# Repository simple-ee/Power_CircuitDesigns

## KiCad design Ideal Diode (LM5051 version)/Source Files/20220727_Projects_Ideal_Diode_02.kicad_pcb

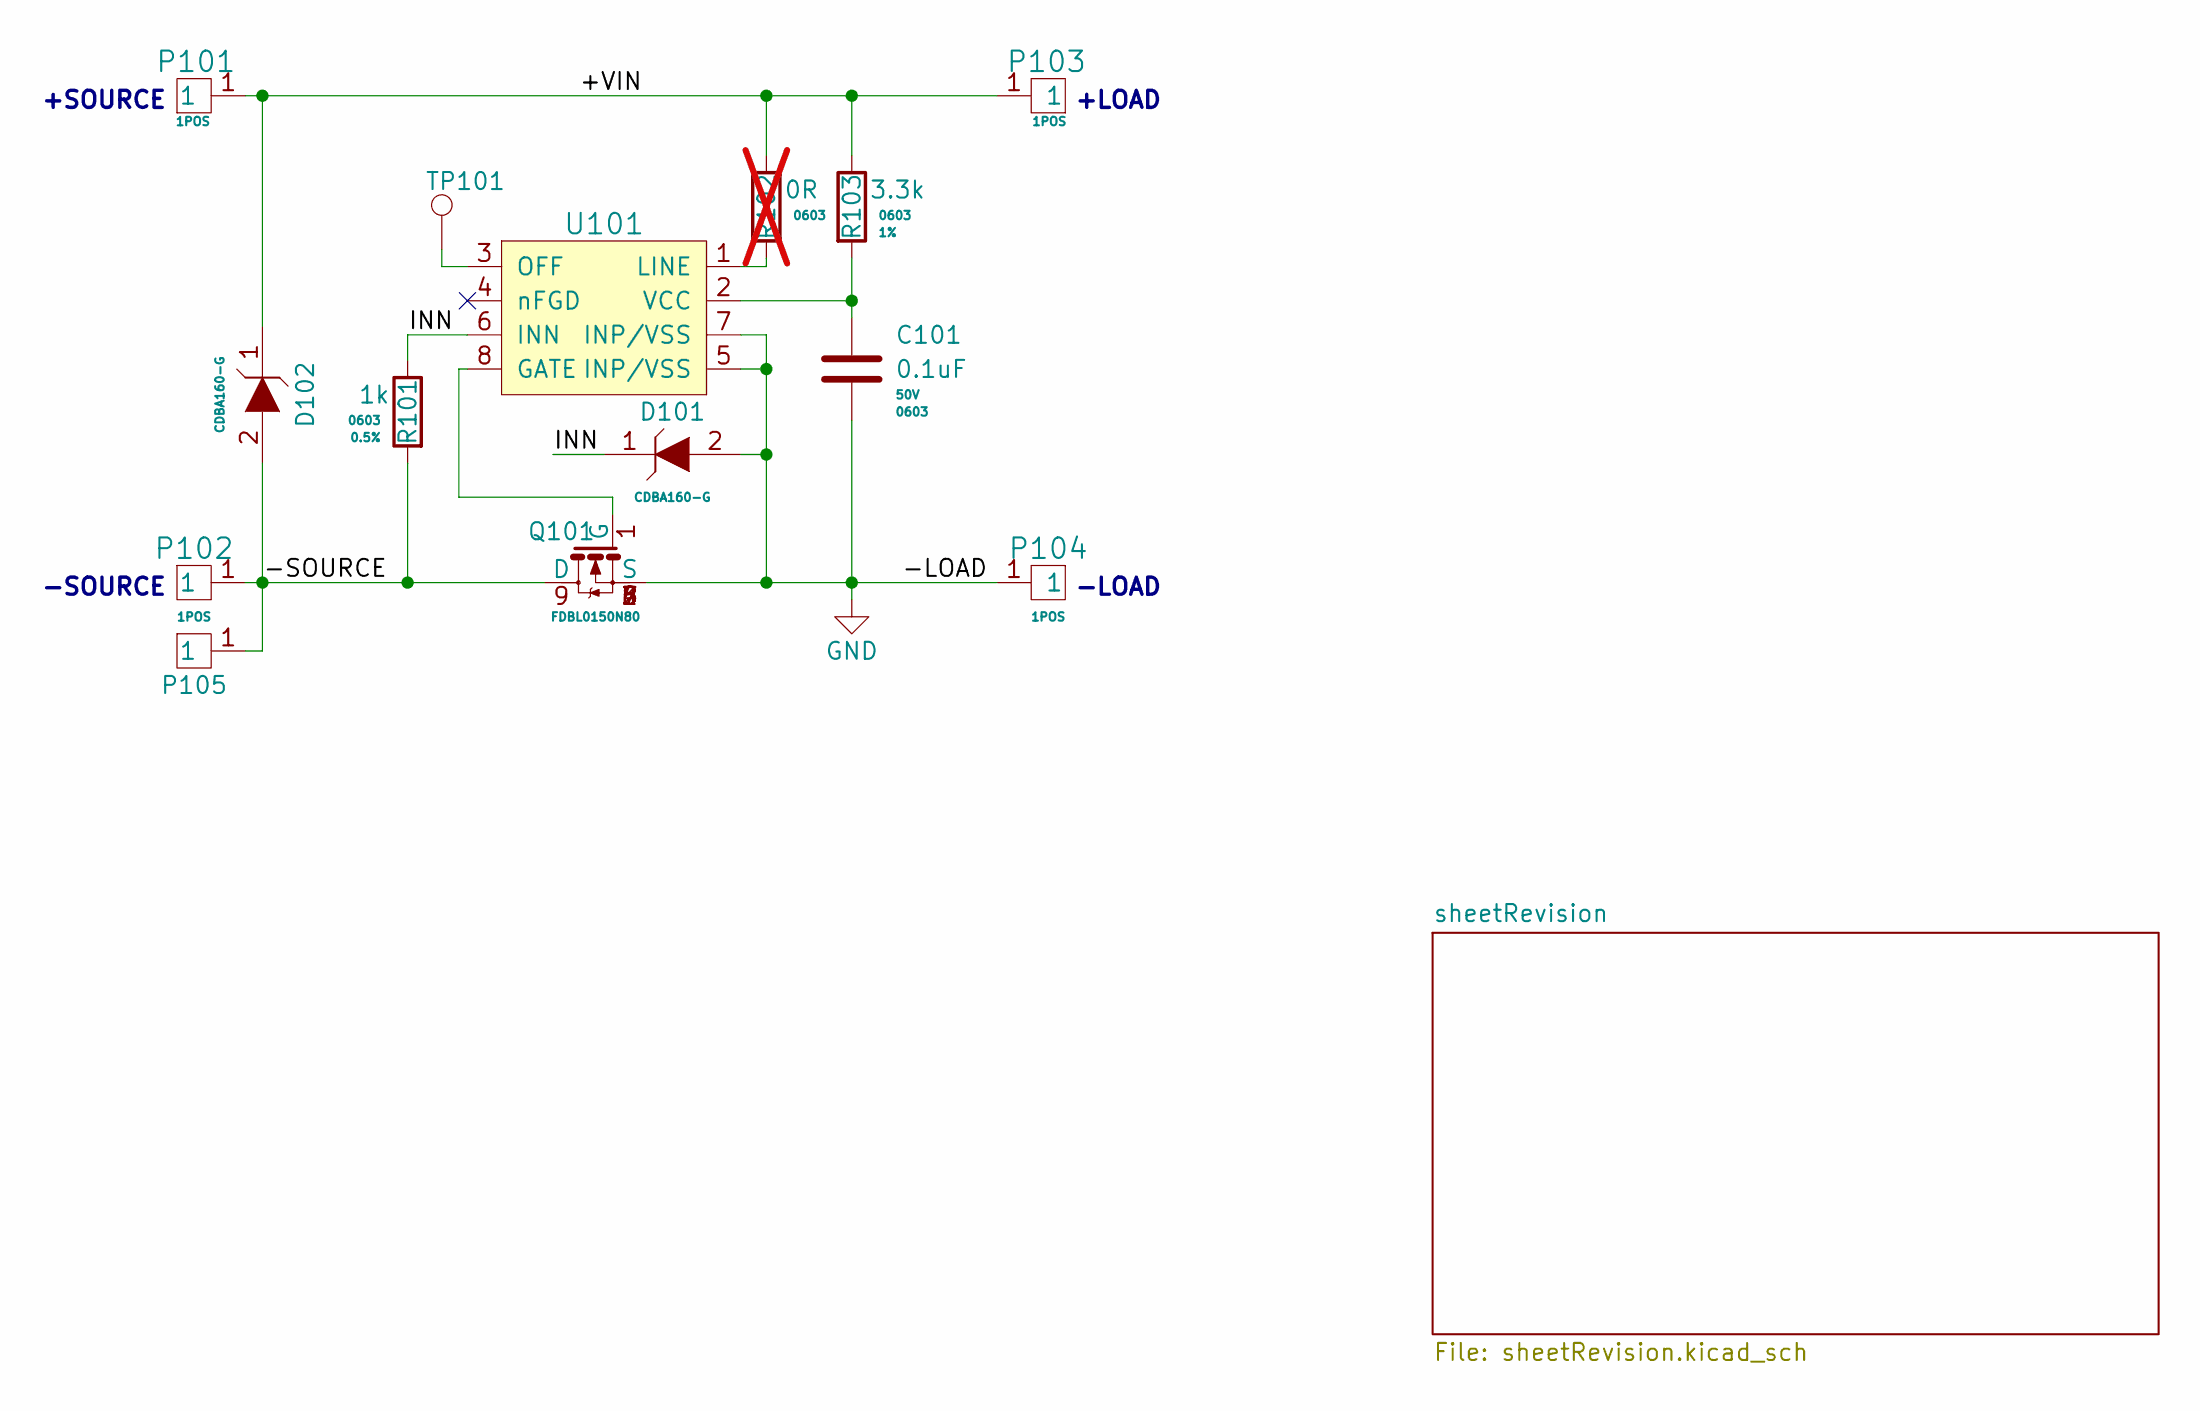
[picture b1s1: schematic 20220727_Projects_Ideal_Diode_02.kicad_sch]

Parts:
C101: C0603C104K5RACAUTO; C_0603_Handsolder
D101, D102: CDBA160-G; D_SMA
P101, P103: TH_1POS_3.4MM_M3; TH_1POS_3.4MMxM3
P102, P104: TH_1POS_12MM_M5; TH_1POS_12MMxM5
P105: Heatsink_28x28x10mm; Manufacturer ###
Q101: FDBL0150N80; HPSOF-8
R101: RR0816P-102-D; R_0603_Handsolder
R102: RMCF0603ZT0R00; R_0603_Handsolder; not fitted
R103: RC0603FR-073K3L; R_0603_Handsolder
TP101: TestPoint_D1MM; TestPoint_Pad_D1.0mm
U101: LM5051MAX_NOPB; SOIC-8

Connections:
/+VIN: D102.1 (K), P101.1, P103.1, R102.1, R103.1
/-SOURCE: D102.2 (A), P102.1, P105.1, Q101.9 (D), R101.2
/INN: D101.1 (K), R101.1, U101.6 (INN)
GND: C101.2, D101.2 (A), P104.1, Q101.2 (S), Q101.3 (S), Q101.4 (S), Q101.5 (S), Q101.6 (S), Q101.7 (S), Q101.8 (S), U101.5 (INP/VSS), U101.7 (INP/VSS)
unnamed: Q101.1 (G), U101.8 (GATE)
unnamed: R102.2, U101.1 (LINE)
unnamed: TP101.1, U101.3 (OFF)
unnamed: C101.1, R103.2, U101.2 (VCC)

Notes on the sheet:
-LOAD
+LOAD
-SOURCE
+SOURCE

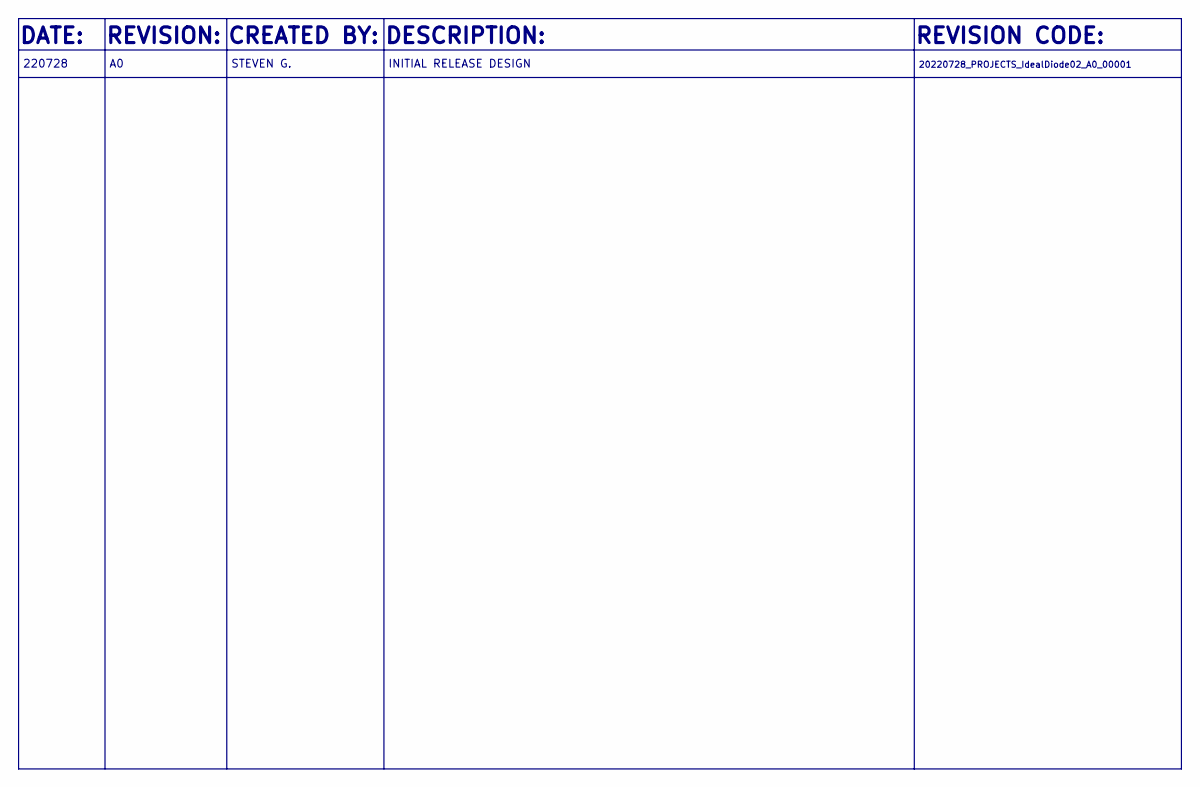
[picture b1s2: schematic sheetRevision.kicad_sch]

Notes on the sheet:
INITIAL RELEASE DESIGN
20220728_PROJECTS_IdealDiode02_A0_00001
220728
REVISION:
STEVEN G.
REVISION CODE:
DESCRIPTION:
DATE:
CREATED BY:

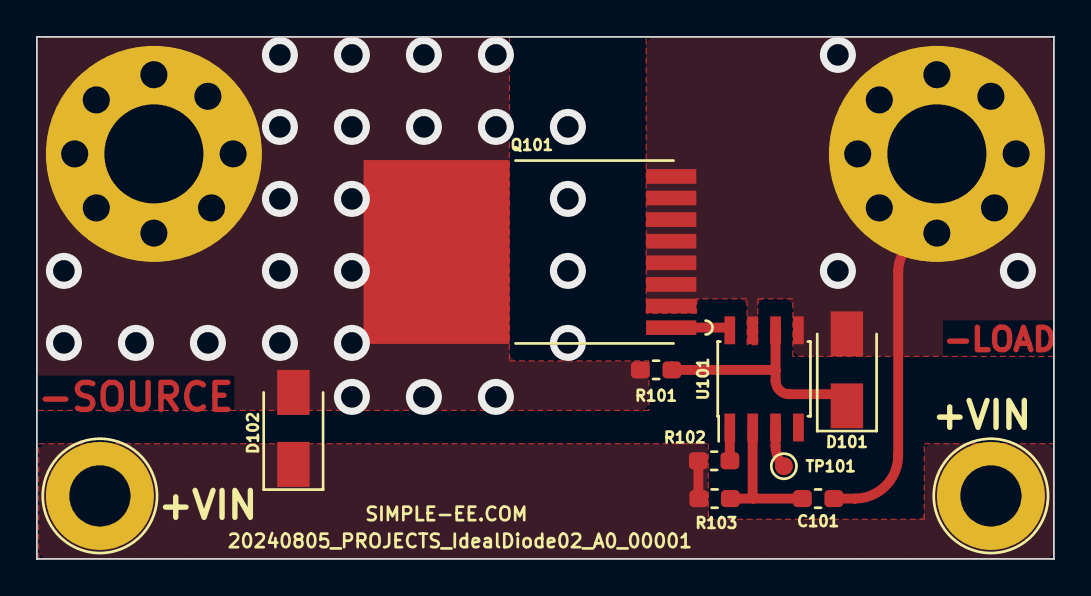
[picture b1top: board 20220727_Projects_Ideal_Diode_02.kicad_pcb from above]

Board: 2 copper layers, 56.5 x 29.0 mm, 14 parts (1 on the bottom side), 8 nets.

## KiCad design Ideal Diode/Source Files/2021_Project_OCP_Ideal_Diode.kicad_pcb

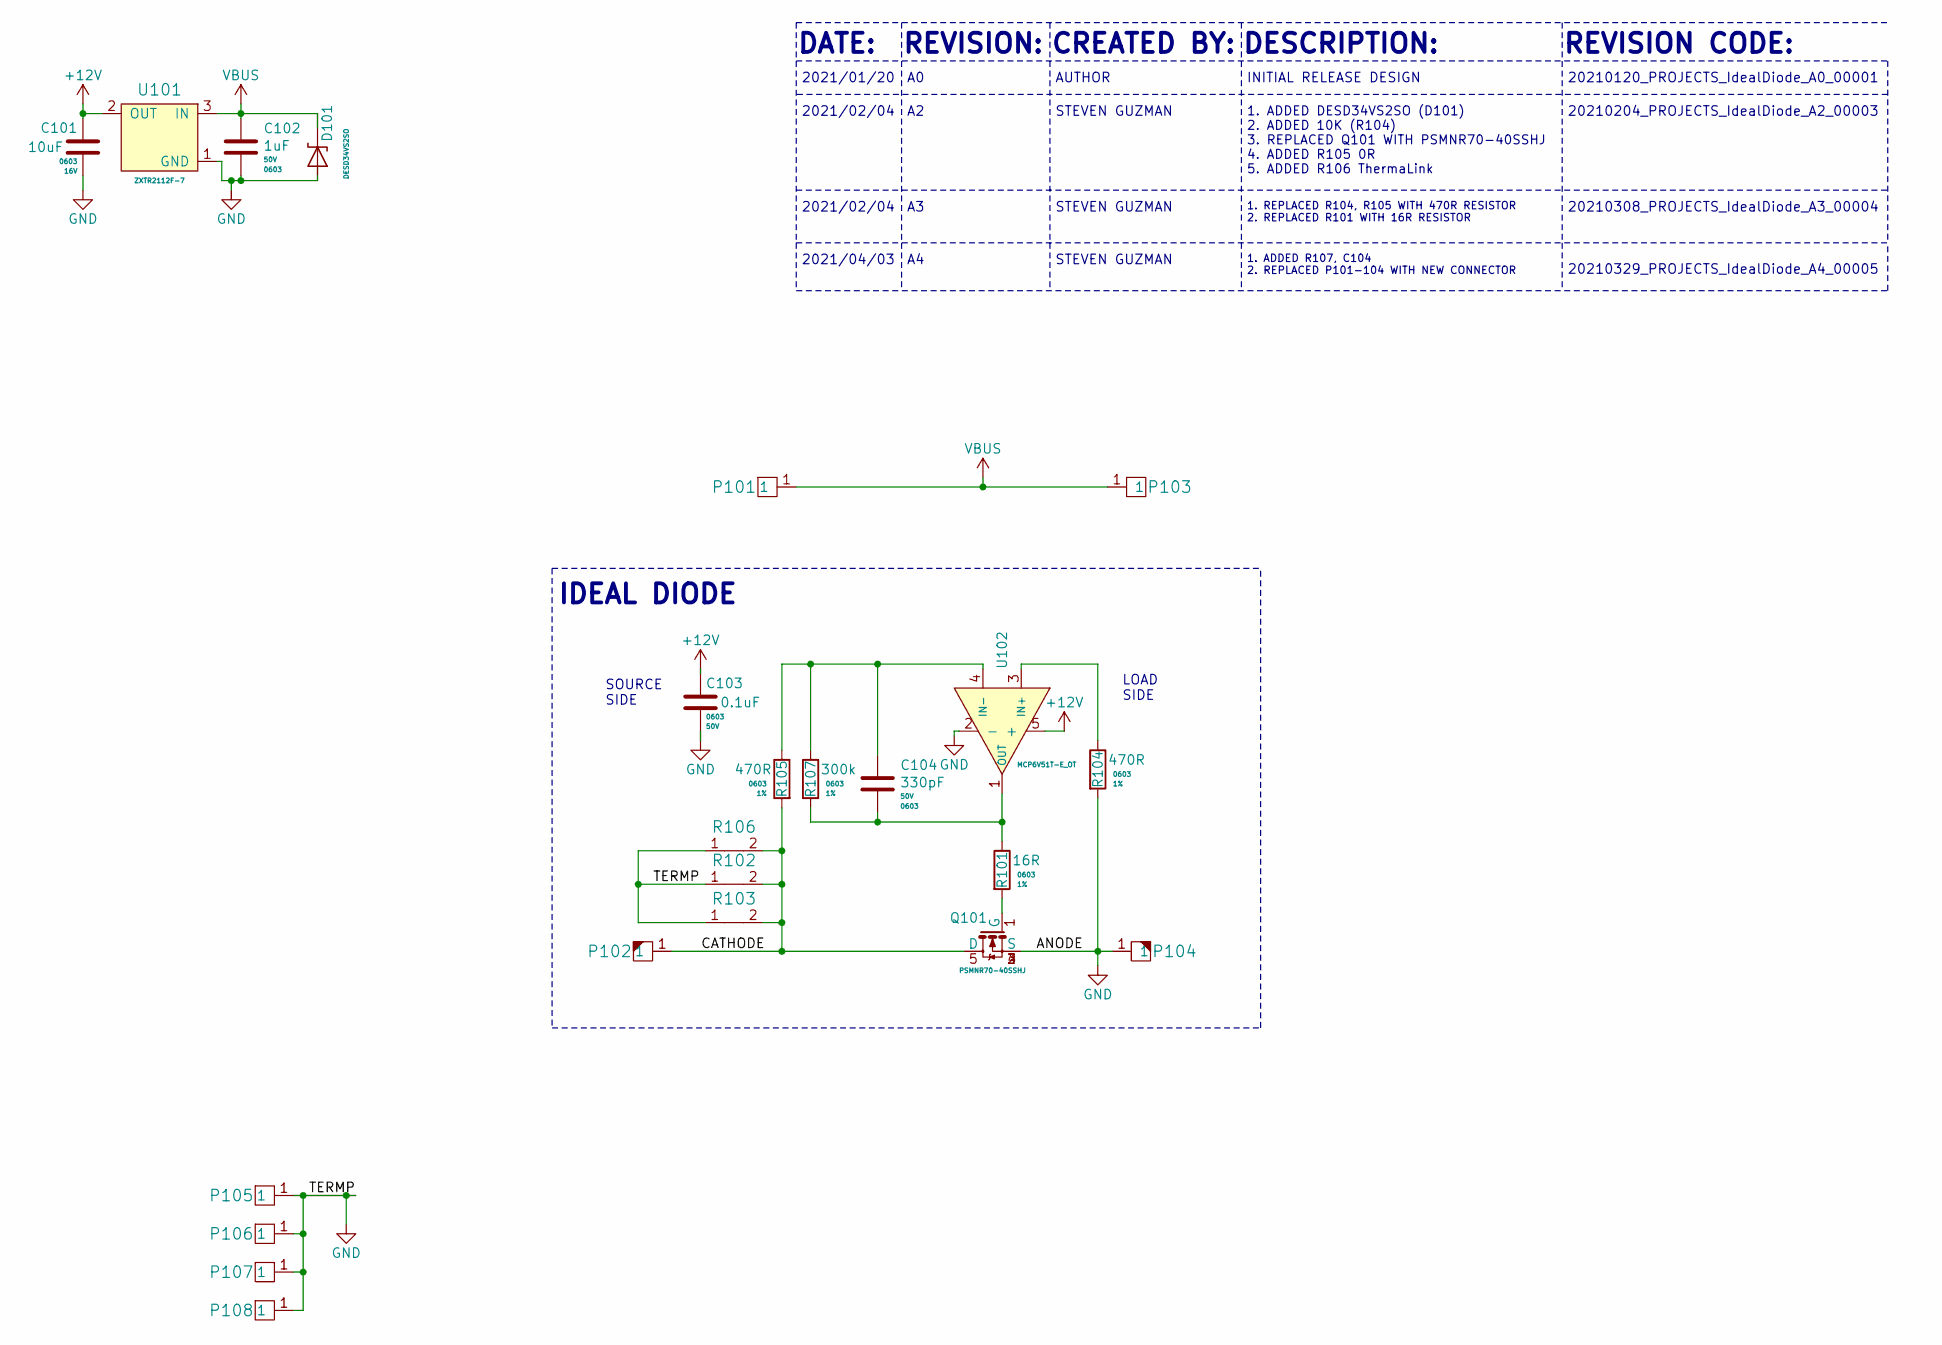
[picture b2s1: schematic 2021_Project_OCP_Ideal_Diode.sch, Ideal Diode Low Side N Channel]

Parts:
C101: CL10X106MO8NRNC; C_0603_Handsolder
C102: CL10A105KB8NNNC; C_0603_Handsolder
C103: C0603C104K5RACAUTO; C_0603_Handsolder
C104: C0603C331J5GACTU; C_0603_Handsolder
D101: DESD34VS2SO; SOT-23-3
P101, P103: 2.5x2.5mm_pad; pad_2.5x2.5mm
P102, P104: 7460305; 7460305_HASL
P105, P106, P107, P108: MH_1POS_2.5MM; MountingHole_2.5mm_Pad_Via
Q101: PSMNR70-40SSHJ; SOT-1235
R101: RC0603FR-0716RL; R_0603_Handsolder
R102, R103, R106: THJP0612AST1
R104, R105: RC0603FR-07470RL; R_0603_Handsolder
R107: RMCF0603FT300K; R_0603_Handsolder
U101: ZXTR2112F-7; SOT-23-3
U102: MCP6V51T-E_OT; SOT-23-5_HandSoldering

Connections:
+12V: C101.1, C103.1, U101.2 (OUT), U102.5 (+)
/CATHODE: P102.1, Q101.5 (D), R102.2, R103.2, R105.2, R106.2
GND: C101.2, C102.2, C103.2, D101.1 (A), D101.2 (A), P104.1, P105.1, P106.1, P107.1, P108.1, Q101.2 (S), Q101.3 (S), Q101.4 (S), R102.1, R103.1, R104.2, R106.1, U101.1 (GND), U102.2 (-)
unnamed: C104.1, R105.1, R107.1, U102.4 (IN-)
unnamed: C104.2, R101.1, R107.2, U102.1 (OUT)
unnamed: Q101.1 (G), R101.2
unnamed: R104.1, U102.3 (IN+)
VBUS: C102.1, D101.3 (K), P101.1, P103.1, U101.3 (IN)

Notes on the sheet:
DATE:
DESCRIPTION:
REVISION:
REVISION CODE:
2021/01/20
CREATED BY:
AUTHOR
20210120_PROJECTS_IdealDiode_A0_00001
SOURCE SIDE
LOAD SIDE
INITIAL RELEASE DESIGN
IDEAL DIODE
1. ADDED DESD34VS2SO (D101) 2. ADDED 10K (R104) 3. REPLACED Q101 WITH PSMNR70-40SSHJ 4. ADDED R105 0R 5. ADDED R106 ThermaLink
2021/02/04
20210204_PROJECTS_IdealDiode_A2_00003
STEVEN GUZMAN
1. REPLACED R104, R105 WITH 470R RESISTOR 2. REPLACED R101 WITH 16R RESISTOR
20210308_PROJECTS_IdealDiode_A3_00004
2021/04/03
1. ADDED R107, C104 2. REPLACED P101-104 WITH NEW CONNECTOR
20210329_PROJECTS_IdealDiode_A4_00005

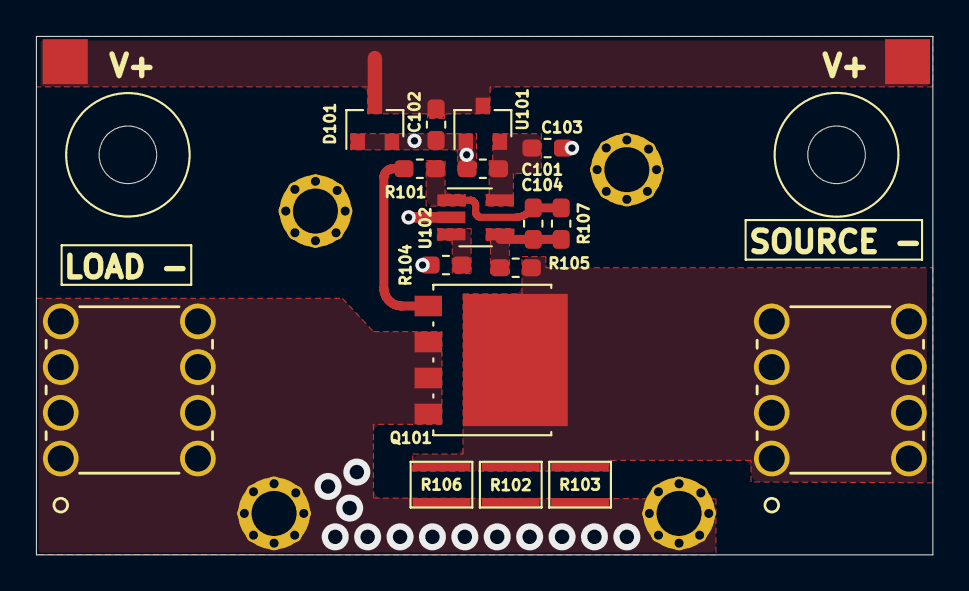
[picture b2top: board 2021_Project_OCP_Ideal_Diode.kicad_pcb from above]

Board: 2 copper layers, 49.8 x 28.8 mm, 23 parts (0 on the bottom side), 8 nets.

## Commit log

2021-02-15 Create Ideal Diode
2021-02-15 Create T
2021-03-08 Add files via upload
    Version 3 release:
    1. Updated R104 and R105 to 470R resistor value for better reverse current protection
    2. Updated R101 for better stability when in reverse current when using a switch mode power supply as the source. Higher switching frequencies in reverse current condition causes oscillation in the o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
2021-05-03 Version A4
    Updated to Version A4 of ideal diode
2024-08-06 New version using LM5051 from texas instrument
    This is an updated version of the ideal diode using LM5051. The last version was a discrete version using a zero-drift op amp and will later update that version as well but for a quick solution and l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

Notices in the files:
parts and their libraries:
Copyright 2016 Accelerated Designs. All rights reserved.
